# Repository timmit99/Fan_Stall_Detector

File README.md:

# Fan Failure Detection Board
This board is able to detect a stalled fan and set an output to trigger external actions.

## Overview
This board uses the MAX6684 IC and some support parts to detect the current flowing through the fan and sets outputs based on disruptions in that current flow. By varying the value of capacitor `C3` the system can be tuned for different fans. "Because  of  the  complexity  of  fan-current  waveforms, the  value  of  CF has  to  be  arrived  at  empirically  and must  be  verified  by  bench  testing." [From the datasheet](https://www.analog.com/media/en/technical-documentation/data-sheets/max6684.pdf). The datasheet recommends 0.1uF as the starting point

### Setup
To use, connect your fan to the "Fan Out" connector, fan power supply to "Fan Power In", and 3v3/Gnd to the 4 pin JST header. The fan will turn on automatically when 3v3 is applied. To turn the fan off, pull the fan enable pin "FanEn" low. When the fan enters a locked-rotor condition, the Fail pin "~{Fail}" is pulled low.

## BOM

| Reference | Description  |                            Note                               | Quantity |   LCSC  |
|   :---:   |     :---:    |                            :---:                              |  :---:   |  :---:  |
|  C1, C3   |    0.1 uF    |                      C_0805_2012Metric                        |     2    | C49678  |
|    C2     |    1 uF      |                      C_0805_2012Metric                        |     1    | C28323  |
|  R2, R3   |    1K        |                      R_0805_2012Metric                        |     2    | C17513  |
|    R1     |    10K       |                      R_0805_2012Metric                        |     1    | C17414  |
|  D1, D2   |    LED       |                     LED_0805_2012Metric                       |     2    | C84256  |
|    U1     |    MAX6684   |                  SO-8_3.9x4.9mm_P1.27mm                       |     1    | C143563 |
|    J1     |  Conn_01x04  |             JST_XH_B4B-XH-A_1x04_P2.50mm_Vertical             |     1    | C144395 |
|  J2, J3   | Fan, PowerIn | TerminalBlock_Phoenix_MKDS-1,5-2-5.08_1x02_P5.08mm_Horizontal |     2    |  C8465  |
|  J4, J5   |    FC-, FC+  |                PinHeader_1x01_P2.54mm_Vertical                |     2    | C492400 |

### [Interactive BOM](http://htmlpreview.github.io/?https://github.com/timmit99/Fan_Stall_Detector/blob/main/iBOM/FanStallDetector.html)

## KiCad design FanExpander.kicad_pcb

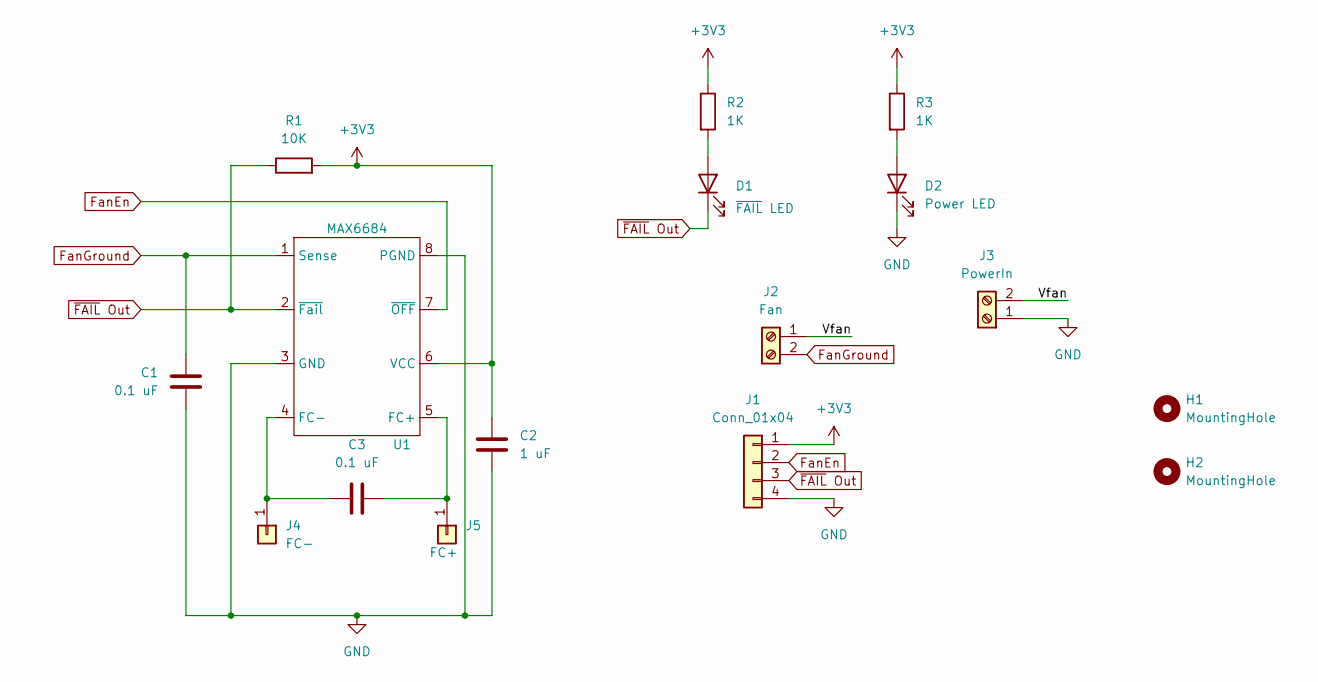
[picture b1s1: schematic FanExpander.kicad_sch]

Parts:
C1, C3: 0.1 uF; C_0805_2012Metric
C2: 1 uF; C_0805_2012Metric
D1: ~{FAIL} LED; LED_0805_2012Metric
D2: Power LED; LED_0805_2012Metric
H1, H2: MountingHole; MountingHole_3.2mm_M3
J1: Conn_01x04; JST_XH_B4B-XH-A_1x04_P2.50mm_Vertical
J2: Fan; TerminalBlock_Phoenix_MKDS-1,5-2-5.08_1x02_P5.08mm_Horizont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
J3: PowerIn; TerminalBlock_Phoenix_MKDS-1,5-2-5.08_1x02_P5.08mm_Horizont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
J4: FC-; PinHeader_1x01_P2.54mm_Vertical
J5: FC+; PinHeader_1x01_P2.54mm_Vertical
R1: 10K; R_0805_2012Metric
R2, R3: 1K; R_0805_2012Metric
U1: MAX6684; SO-8_3.9x4.9mm_P1.27mm

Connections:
+3V3: C2.1, J1.1, R1.2, R2.1, R3.1, U1.6 (VCC)
/Vfan: J2.1, J3.2
FanEn: J1.2, U1.7 (~OFF)
FanGround: C1.2, J2.2, U1.1 (Sense)
GND: C1.1, C2.2, D2.1 (K), J1.4, J3.1, U1.3 (GND), U1.8 (PGND)
unnamed: C3.1, J4.1, U1.4 (FC-)
unnamed: C3.2, J5.1, U1.5 (FC+)
unnamed: D1.2 (A), R2.2
unnamed: D2.2 (A), R3.2
~FAIL Out: D1.1 (K), J1.3, R1.1, U1.2 (~Fail)

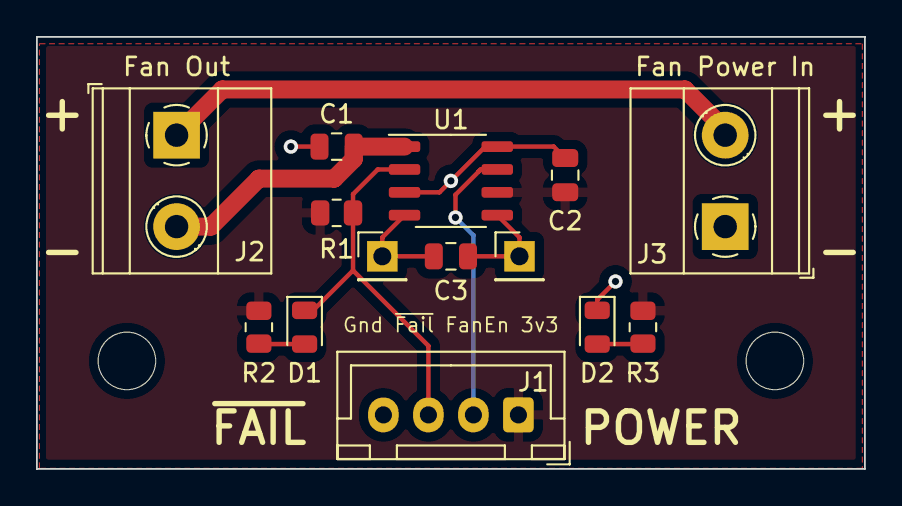
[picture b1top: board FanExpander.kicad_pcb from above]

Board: 2 copper layers, 46.0 x 24.0 mm, 16 parts (0 on the bottom side), 10 nets.

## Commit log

2022-12-16 Update Wiring_Diagram.png
    Wording change for Fan control pin.
